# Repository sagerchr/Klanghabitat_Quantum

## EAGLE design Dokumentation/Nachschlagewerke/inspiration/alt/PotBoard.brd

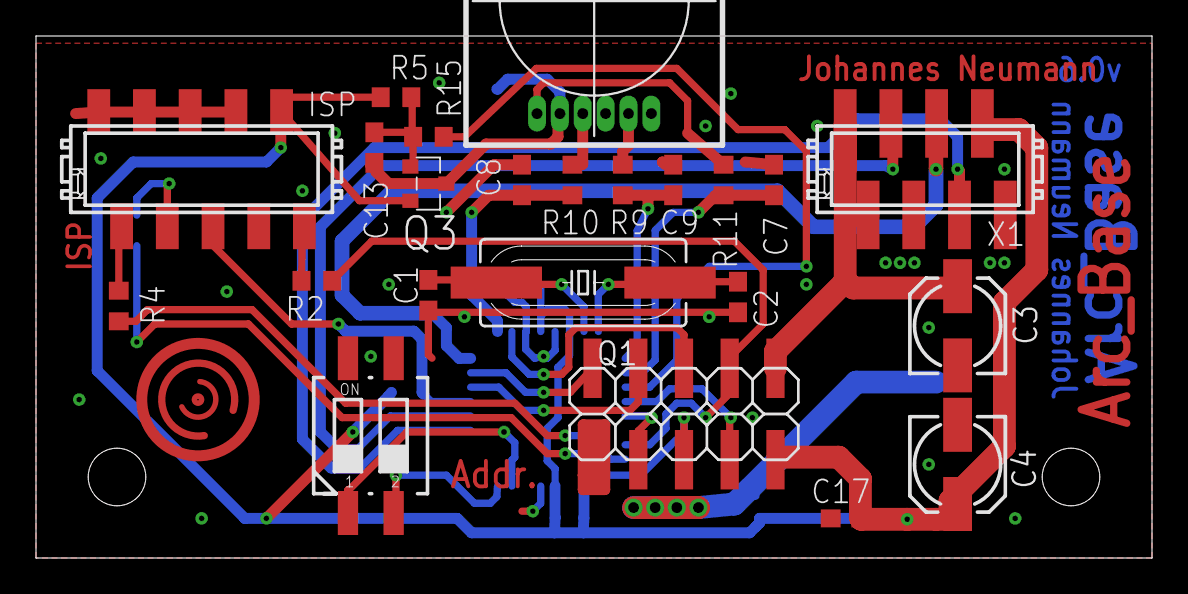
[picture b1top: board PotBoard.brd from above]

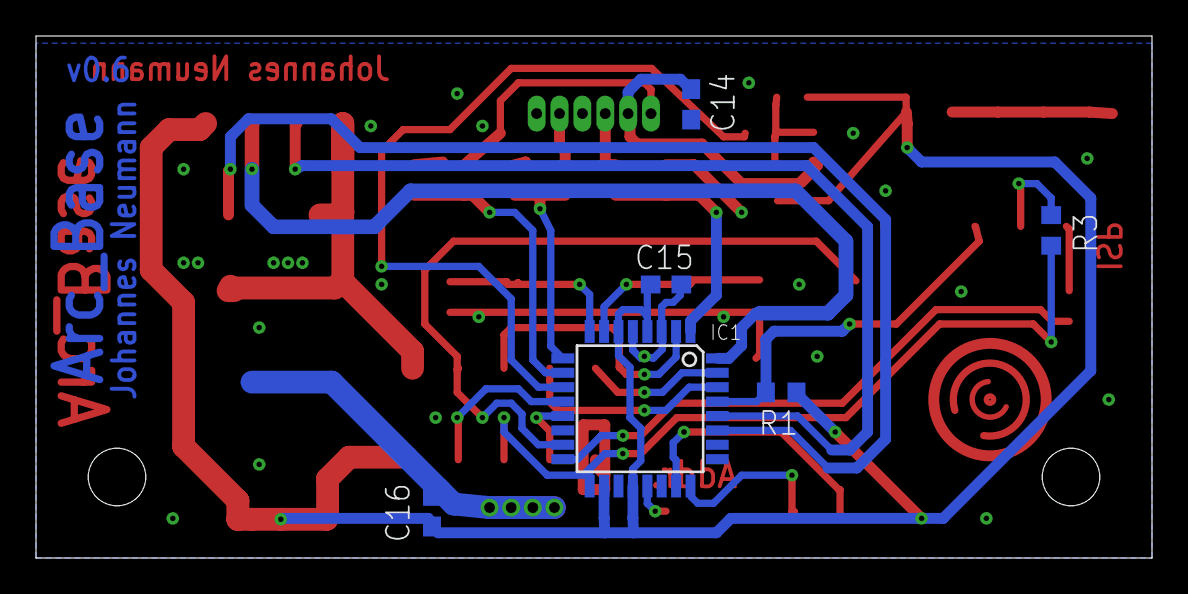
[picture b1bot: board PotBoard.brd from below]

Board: 2 copper layers, 62.0 x 29.0 mm, 29 parts (6 on the bottom side), 31 nets.

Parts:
ADRESS: 219-02; CTS-219-02
C1, C2: 22p; C0603
C3, C4: 10u; 153CLV-0505
C7, C8, C9: 10n; C0603
C13, C14, C15, C16, C17: 100n; C0603
IC1: MEGA8-AI; TQFP32-08
ISP: MICROMATCH-10-SMD
JP4: 2X05SMD
Q1: 20MHz; SM49
Q3: IRLML5203; MICRO3
R1, R5: 10k; R0603
R2, R3, R4: 330; R0603
R9, R10, R11: 4k7; R0603
R15: 1k; R0603
U$1: BOURNS_EM14; BOURNS_EM14_AXIAL
X1: MICROMATCH-8SMD; MICROMATCH-8-SMD

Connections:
+3V3: C3.+, JP4.10, X1.1, X1.2
CHANNEL-A: C9.2, IC1.9, R9.2
CHANNEL-B: C7.2, IC1.10, R11.2
GND: ADRESS.3, ADRESS.4, C1.1, C2.1, C3.-, C4.-, C7.1, C8.1, C9.1, C14.1, C15.1, C16.1, C17.1, IC1.3, IC1.5, IC1.21, ISP.P$4, ISP.P$6, ISP.P$8, ISP.P$10, JP4.1, U$1.P$1, U$1.P$3, X1.4, X1.8
GS_CLK: IC1.13, JP4.3
INT: IC1.32, X1.5
MISO: IC1.16, R4.2
MOSI: IC1.15, JP4.8, R2.2
unnamed: C1.2, IC1.7, Q1.2
unnamed: C2.2, IC1.8, Q1.1
unnamed: ISP.P$1, R2.1
unnamed: ISP.P$7, R3.1
unnamed: ISP.P$9, R4.1
unnamed: ADRESS.1, IC1.23
unnamed: ADRESS.2, IC1.24
unnamed: R11.1, U$1.P$6
unnamed: R10.1, U$1.P$4
unnamed: R9.1, U$1.P$2
unnamed: C13.2, Q3.1, R5.2, R15.1
unnamed: C13.1, C14.2, Q3.3, U$1.P$5
PWEN: IC1.11, R15.2
RCK: IC1.2, JP4.6
RESET: IC1.29, ISP.P$5, R1.2
SCK: IC1.17, JP4.5, R3.2
SCL: IC1.28, X1.3
SDA: IC1.27, X1.6
SWITCH: C8.2, IC1.1, R10.2
VCC: C4.+, C15.2, C16.2, C17.2, IC1.4, IC1.6, IC1.18, IC1.20, ISP.P$2, JP4.9, Q3.2, R1.1, R5.1, X1.7
VPRG: IC1.12, JP4.7
XERR: IC1.30, JP4.4
XLAT: IC1.31, JP4.2

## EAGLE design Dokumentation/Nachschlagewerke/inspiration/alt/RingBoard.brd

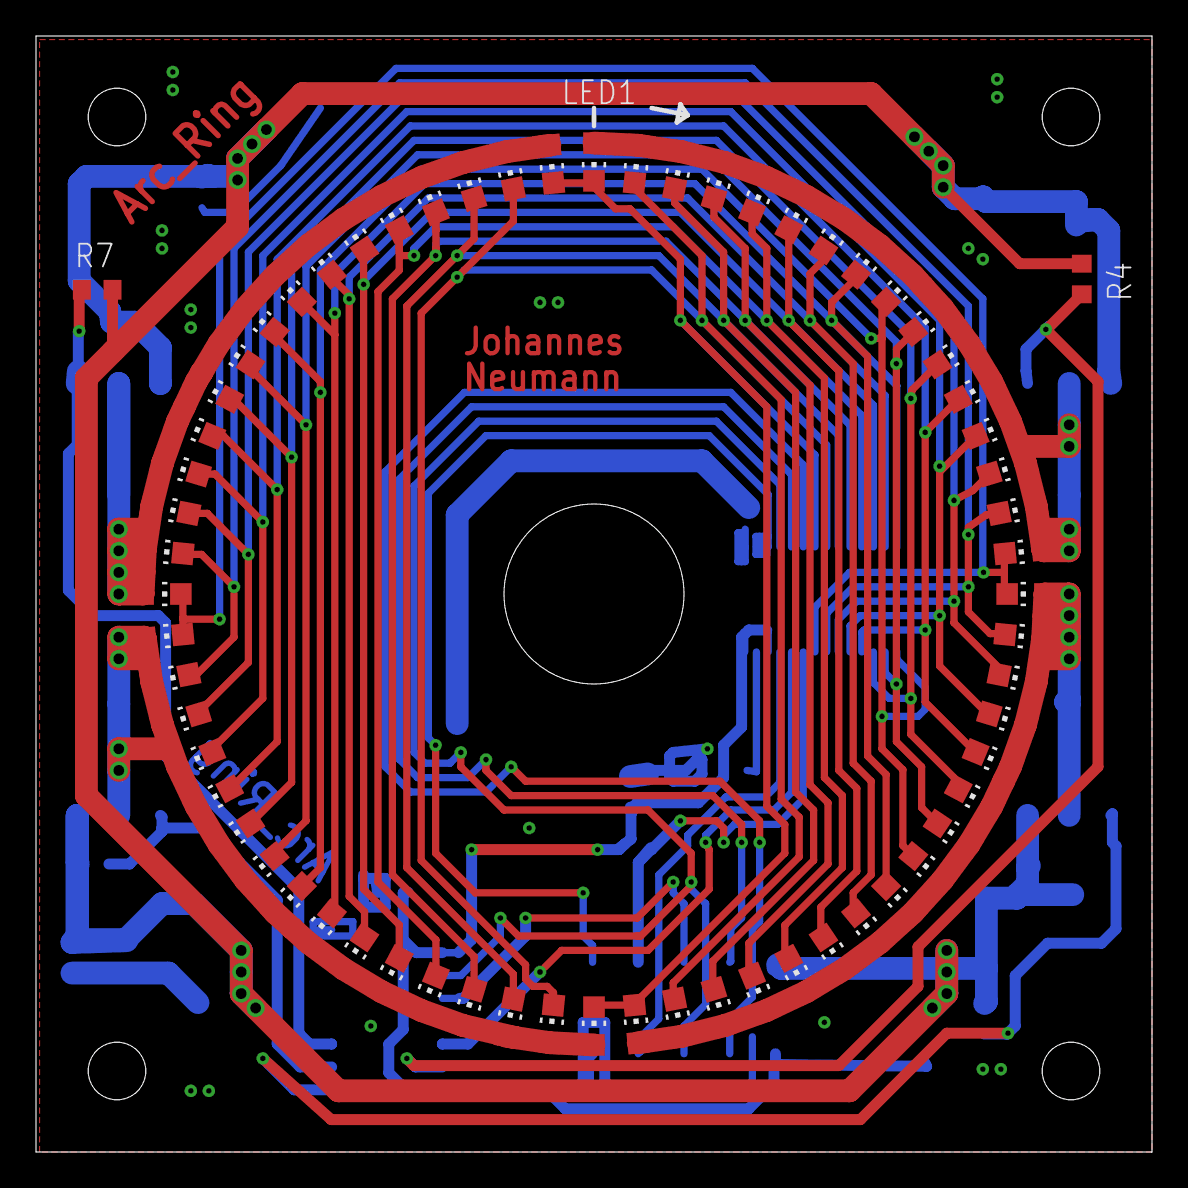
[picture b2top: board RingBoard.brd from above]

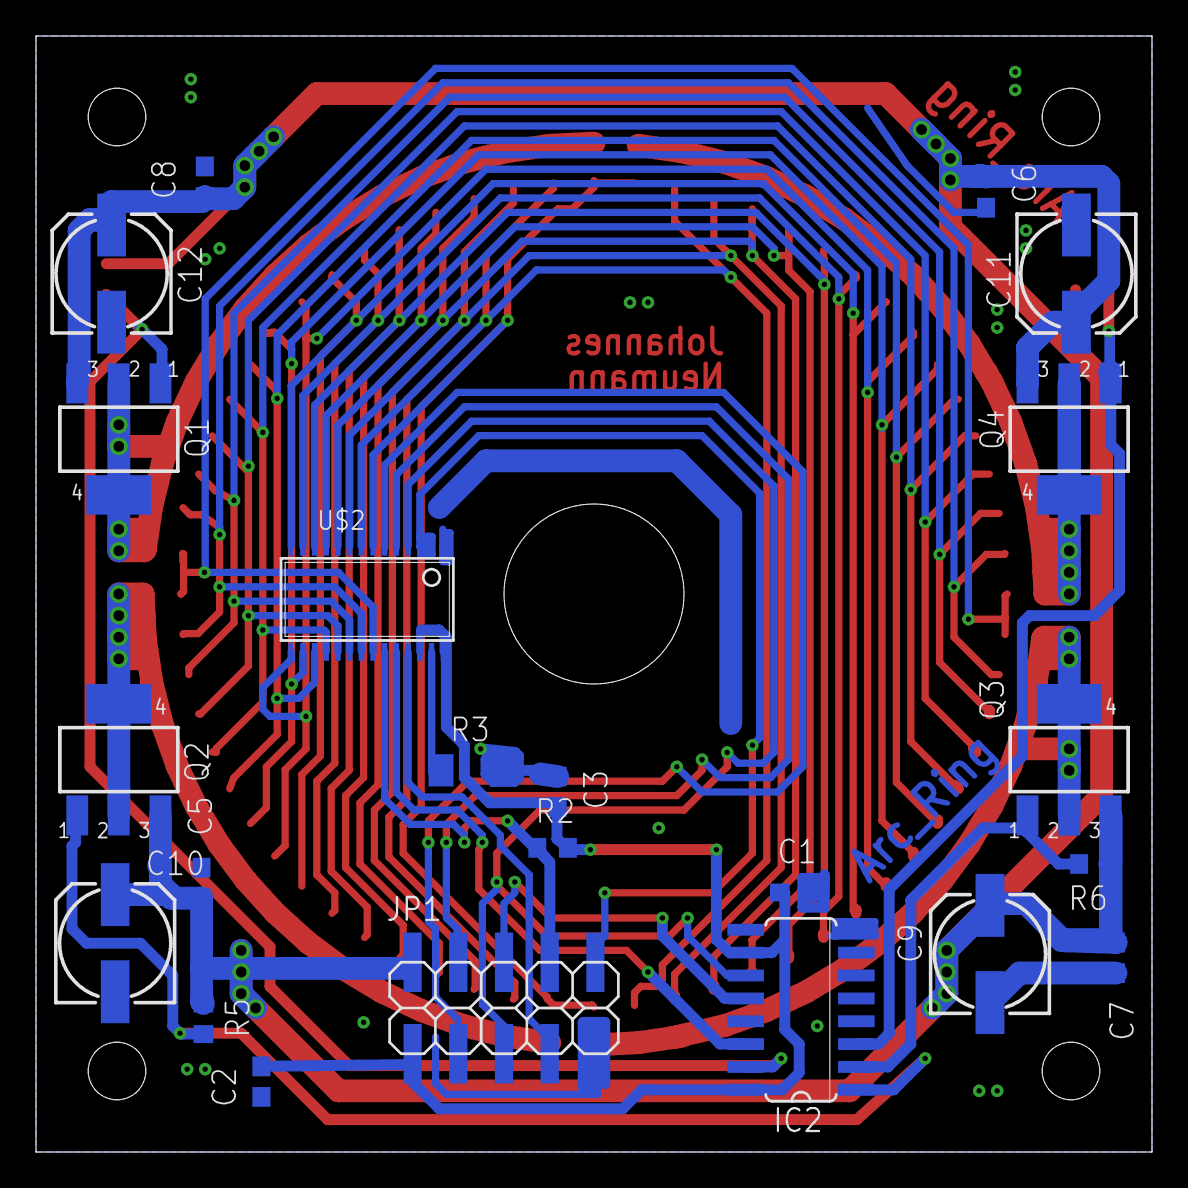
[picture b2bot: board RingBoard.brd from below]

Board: 2 copper layers, 62.0 x 62.0 mm, 88 parts (22 on the bottom side), 36 nets.

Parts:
C1, C2, C3, C5, C6, C7, C8: 100n; C0603
C9, C10, C11, C12: 10u; 153CLV-0605
IC2: 74HC595D; SO16
JP1: 2X05SMD
LED1, LED2, LED3, LED4, LED5, LED6, LED7, LED8, LED9, LED10, LED11, LED12, LED13, LED14, LED15, LED16, LED17, LED18, LED19, LED20, LED21, LED22, LED23, LED24, LED25, LED26, LED27, LED28, LED29, LED30, LED31, LED32, LED33, LED34, LED35, LED36, LED37, LED38, LED39, LED40, LED41, LED42, LED43, LED44, LED45, LED46, LED47, LED48, LED49, LED50, LED51, LED52, LED53, LED54, LED55, LED56, LED57, LED58, LED59, LED60, LED61, LED62, LED63, LED64: CHIP-LED0805
Q1, Q2, Q3, Q4: BSP171P; SOT223
R2: 10k; R0603
R3: I_SET_RESISTOR; M1406
R4, R5, R6, R7: 4k7; R0603
U$2: TLC5940-TSSOP; HTSSOP-28

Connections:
+3V3: C5.1, C6.1, C7.1, C8.1, C9.+, C10.+, C11.+, C12.+, JP1.2, Q1.3, Q2.3, Q3.3, Q4.3, R4.1, R5.1, R6.1, R7.1
COLA: IC2.15, Q1.1, R4.2
COLB: IC2.1, Q2.1, R5.2
COLC: IC2.2, Q3.1, R6.2
COLD: IC2.3, Q4.1, R7.2
D1: LED1.C, LED32.C, LED33.C, LED64.C, U$2.7
D2: LED2.C, LED31.C, LED34.C, LED63.C, U$2.8
D3: LED3.C, LED30.C, LED35.C, LED62.C, U$2.9
D4: LED4.C, LED29.C, LED36.C, LED61.C, U$2.10
D5: LED5.C, LED28.C, LED37.C, LED60.C, U$2.11
D6: LED6.C, LED27.C, LED38.C, LED59.C, U$2.12
D7: LED7.C, LED26.C, LED39.C, LED58.C, U$2.13
D8: LED8.C, LED25.C, LED40.C, LED57.C, U$2.14
D9: LED9.C, LED24.C, LED41.C, LED56.C, U$2.15
D10: LED10.C, LED23.C, LED42.C, LED55.C, U$2.16
D11: LED11.C, LED22.C, LED43.C, LED54.C, U$2.17
D12: LED12.C, LED21.C, LED44.C, LED53.C, U$2.18
D13: LED13.C, LED20.C, LED45.C, LED52.C, U$2.19
D14: LED14.C, LED19.C, LED46.C, LED51.C, U$2.20
D15: LED15.C, LED18.C, LED47.C, LED50.C, U$2.21
D16: LED16.C, LED17.C, LED48.C, LED49.C, U$2.22
GND: C1.2, C2.2, C3.2, C5.2, C6.2, C7.2, C8.2, C9.-, C10.-, C11.-, C12.-, IC2.8, IC2.13, JP1.9, R3.2, U$2.1
GS_CLK: JP1.7, U$2.25
MOSI: JP1.4, U$2.5
unnamed: IC2.14, U$2.24
unnamed: LED17.A, LED18.A, LED19.A, LED20.A, LED21.A, LED22.A, LED23.A, LED24.A, LED25.A, LED26.A, LED27.A, LED28.A, LED29.A, LED30.A, LED31.A, LED32.A, Q2.2, Q2.4
unnamed: LED33.A, LED34.A, LED35.A, LED36.A, LED37.A, LED38.A, LED39.A, LED40.A, LED41.A, LED42.A, LED43.A, LED44.A, LED45.A, LED46.A, LED47.A, LED48.A, Q3.2, Q3.4
unnamed: LED49.A, LED50.A, LED51.A, LED52.A, LED53.A, LED54.A, LED55.A, LED56.A, LED57.A, LED58.A, LED59.A, LED60.A, LED61.A, LED62.A, LED63.A, LED64.A, Q4.2, Q4.4
unnamed: LED1.A, LED2.A, LED3.A, LED4.A, LED5.A, LED6.A, LED7.A, LED8.A, LED9.A, LED10.A, LED11.A, LED12.A, LED13.A, LED14.A, LED15.A, LED16.A, Q1.2, Q1.4
unnamed: R3.1, U$2.27
RCK: IC2.12, JP1.6
SCK: IC2.11, JP1.5, U$2.4
VCC: C1.1, C2.1, C3.1, IC2.10, IC2.16, JP1.1, R2.2, U$2.26, U$2.28
VPRG: JP1.3, U$2.6
XERR: JP1.8, R2.1, U$2.23
XLAT: JP1.10, U$2.2, U$2.3

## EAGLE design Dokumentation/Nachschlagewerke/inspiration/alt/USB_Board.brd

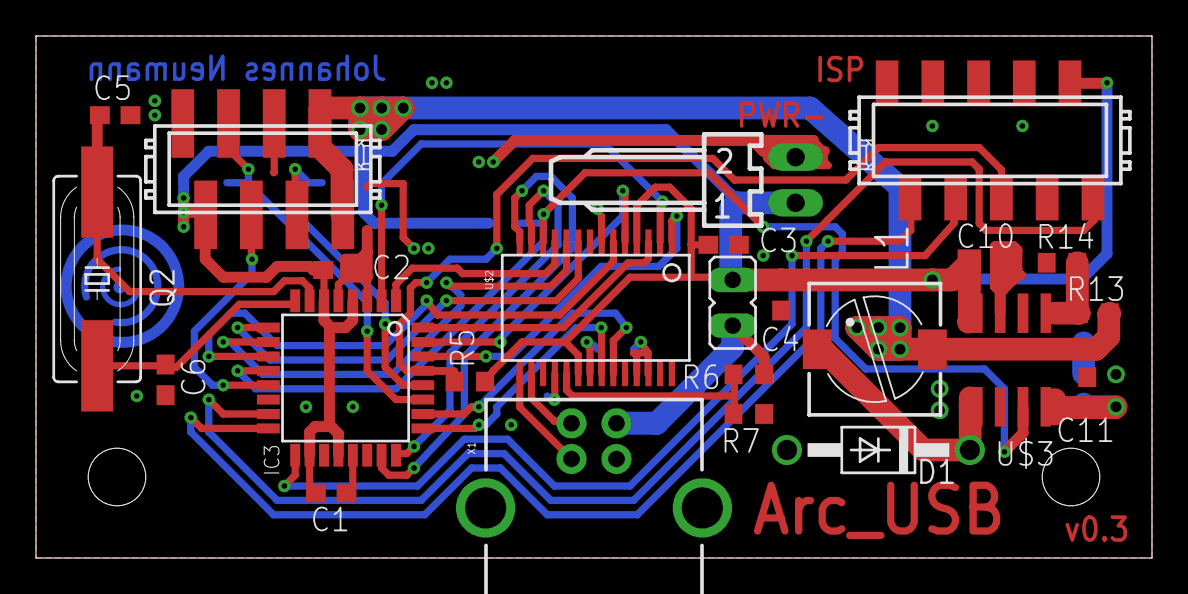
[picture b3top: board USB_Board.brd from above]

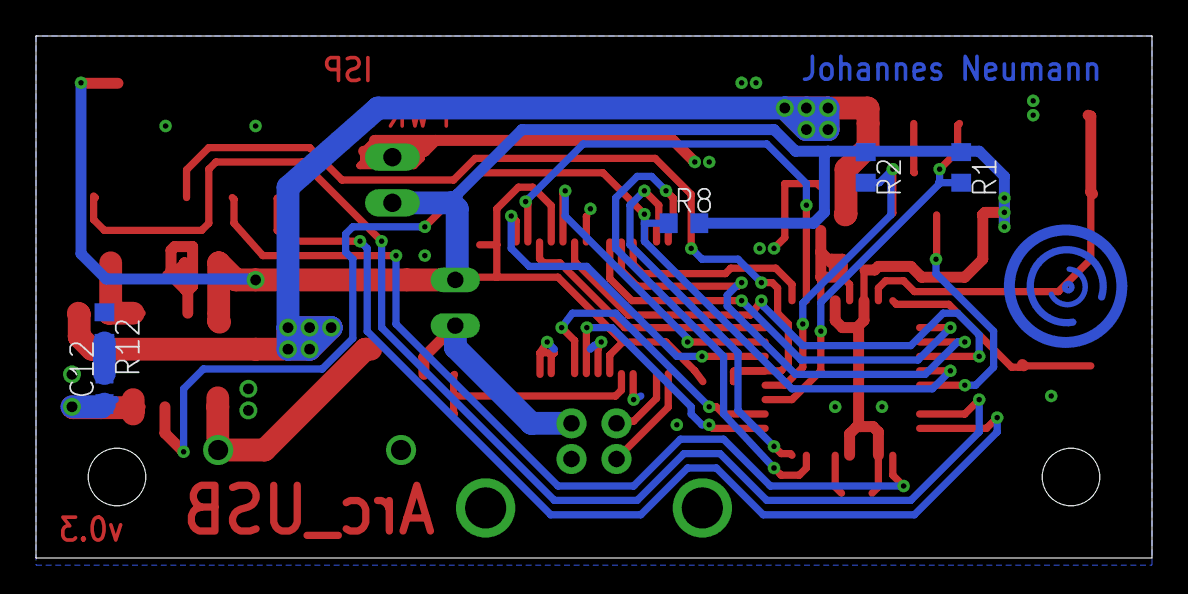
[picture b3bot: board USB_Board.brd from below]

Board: 2 copper layers, 62.0 x 29.0 mm, 29 parts (5 on the bottom side), 33 nets.

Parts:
BUS_PWRD: JP1
C1, C2, C3, C4: 100n; C0603
C5, C6: 22p; C0603
C10: 10uF; C0805
C11: 220p; C0603
C12: 22n; C0603
CONN: MICROMATCH-8SMD; MICROMATCH-8-SMD
D1: MBRS240LT3G; DO41-10
IC3: MEGA8-AI; TQFP32-08
ISP1: MICROMATCH-10-SMD
L1: 15uH; PIS2816
POWER: 22-05-7028-02; 7395-02
Q2: 20MHz; SM49
R1, R2, R14: 3k3; R0603
R5, R7, R8: 10k; R0603
R6, R12: 4k7; R0603
R13: 5k6; R0603
U$2: FT245RL; SSOP28DB
U$3: L5970AD; SO8
X1: USBPTH; USB-B-PTH

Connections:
+3V3: CONN.1, CONN.2, L1.2, R13.2
GND: C1.2, C2.2, C3.2, C4.2, C5.1, C6.1, C10.2, C11.2, CONN.4, CONN.8, D1.A, IC3.3, IC3.5, IC3.21, ISP1.P$4, ISP1.P$6, ISP1.P$8, ISP1.P$10, POWER.2, R7.1, R12.1, R14.1, U$2.7, U$2.18, U$2.21, U$2.25, U$2.26, U$3.7, X1.GND
INT: CONN.5, IC3.13
MISO_2: IC3.16, ISP1.P$9
MOSI_2: IC3.15, ISP1.P$1
unnamed: C5.2, IC3.7, Q2.2
unnamed: C6.2, IC3.8, Q2.1
unnamed: U$2.16, X1.D-
unnamed: IC3.30, U$2.1
unnamed: IC3.31, U$2.5
unnamed: IC3.32, U$2.3
unnamed: IC3.1, U$2.11
unnamed: IC3.2, U$2.2
unnamed: IC3.9, U$2.9
unnamed: IC3.10, U$2.10
unnamed: IC3.11, U$2.6
unnamed: IC3.26, U$2.23
unnamed: IC3.25, U$2.22
unnamed: IC3.24, U$2.13
unnamed: IC3.23, U$2.14
unnamed: D1.C, L1.1, U$3.1
unnamed: BUS_PWRD.2, R6.2, X1.VBUS
unnamed: R13.1, R14.2, U$3.5
unnamed: C12.2, R12.2
unnamed: C11.1, C12.1, U$3.4
PWEN: IC3.12, R8.1, U$2.12, U$3.3
PWR_ON: R6.1, R7.2, U$2.19
RESET_2: IC3.29, ISP1.P$5, R5.2
SCK_2: IC3.17, ISP1.P$7
SCL: CONN.3, IC3.28, R2.2
SDA: CONN.6, IC3.27, R1.2
USB: U$2.15, X1.D+
VCC: BUS_PWRD.1, C1.1, C2.1, C3.1, C4.1, C10.1, CONN.7, IC3.4, IC3.6, IC3.18, IC3.20, ISP1.P$2, POWER.1, R1.1, R2.1, R5.1, R8.2, U$2.4, U$2.20, U$3.8

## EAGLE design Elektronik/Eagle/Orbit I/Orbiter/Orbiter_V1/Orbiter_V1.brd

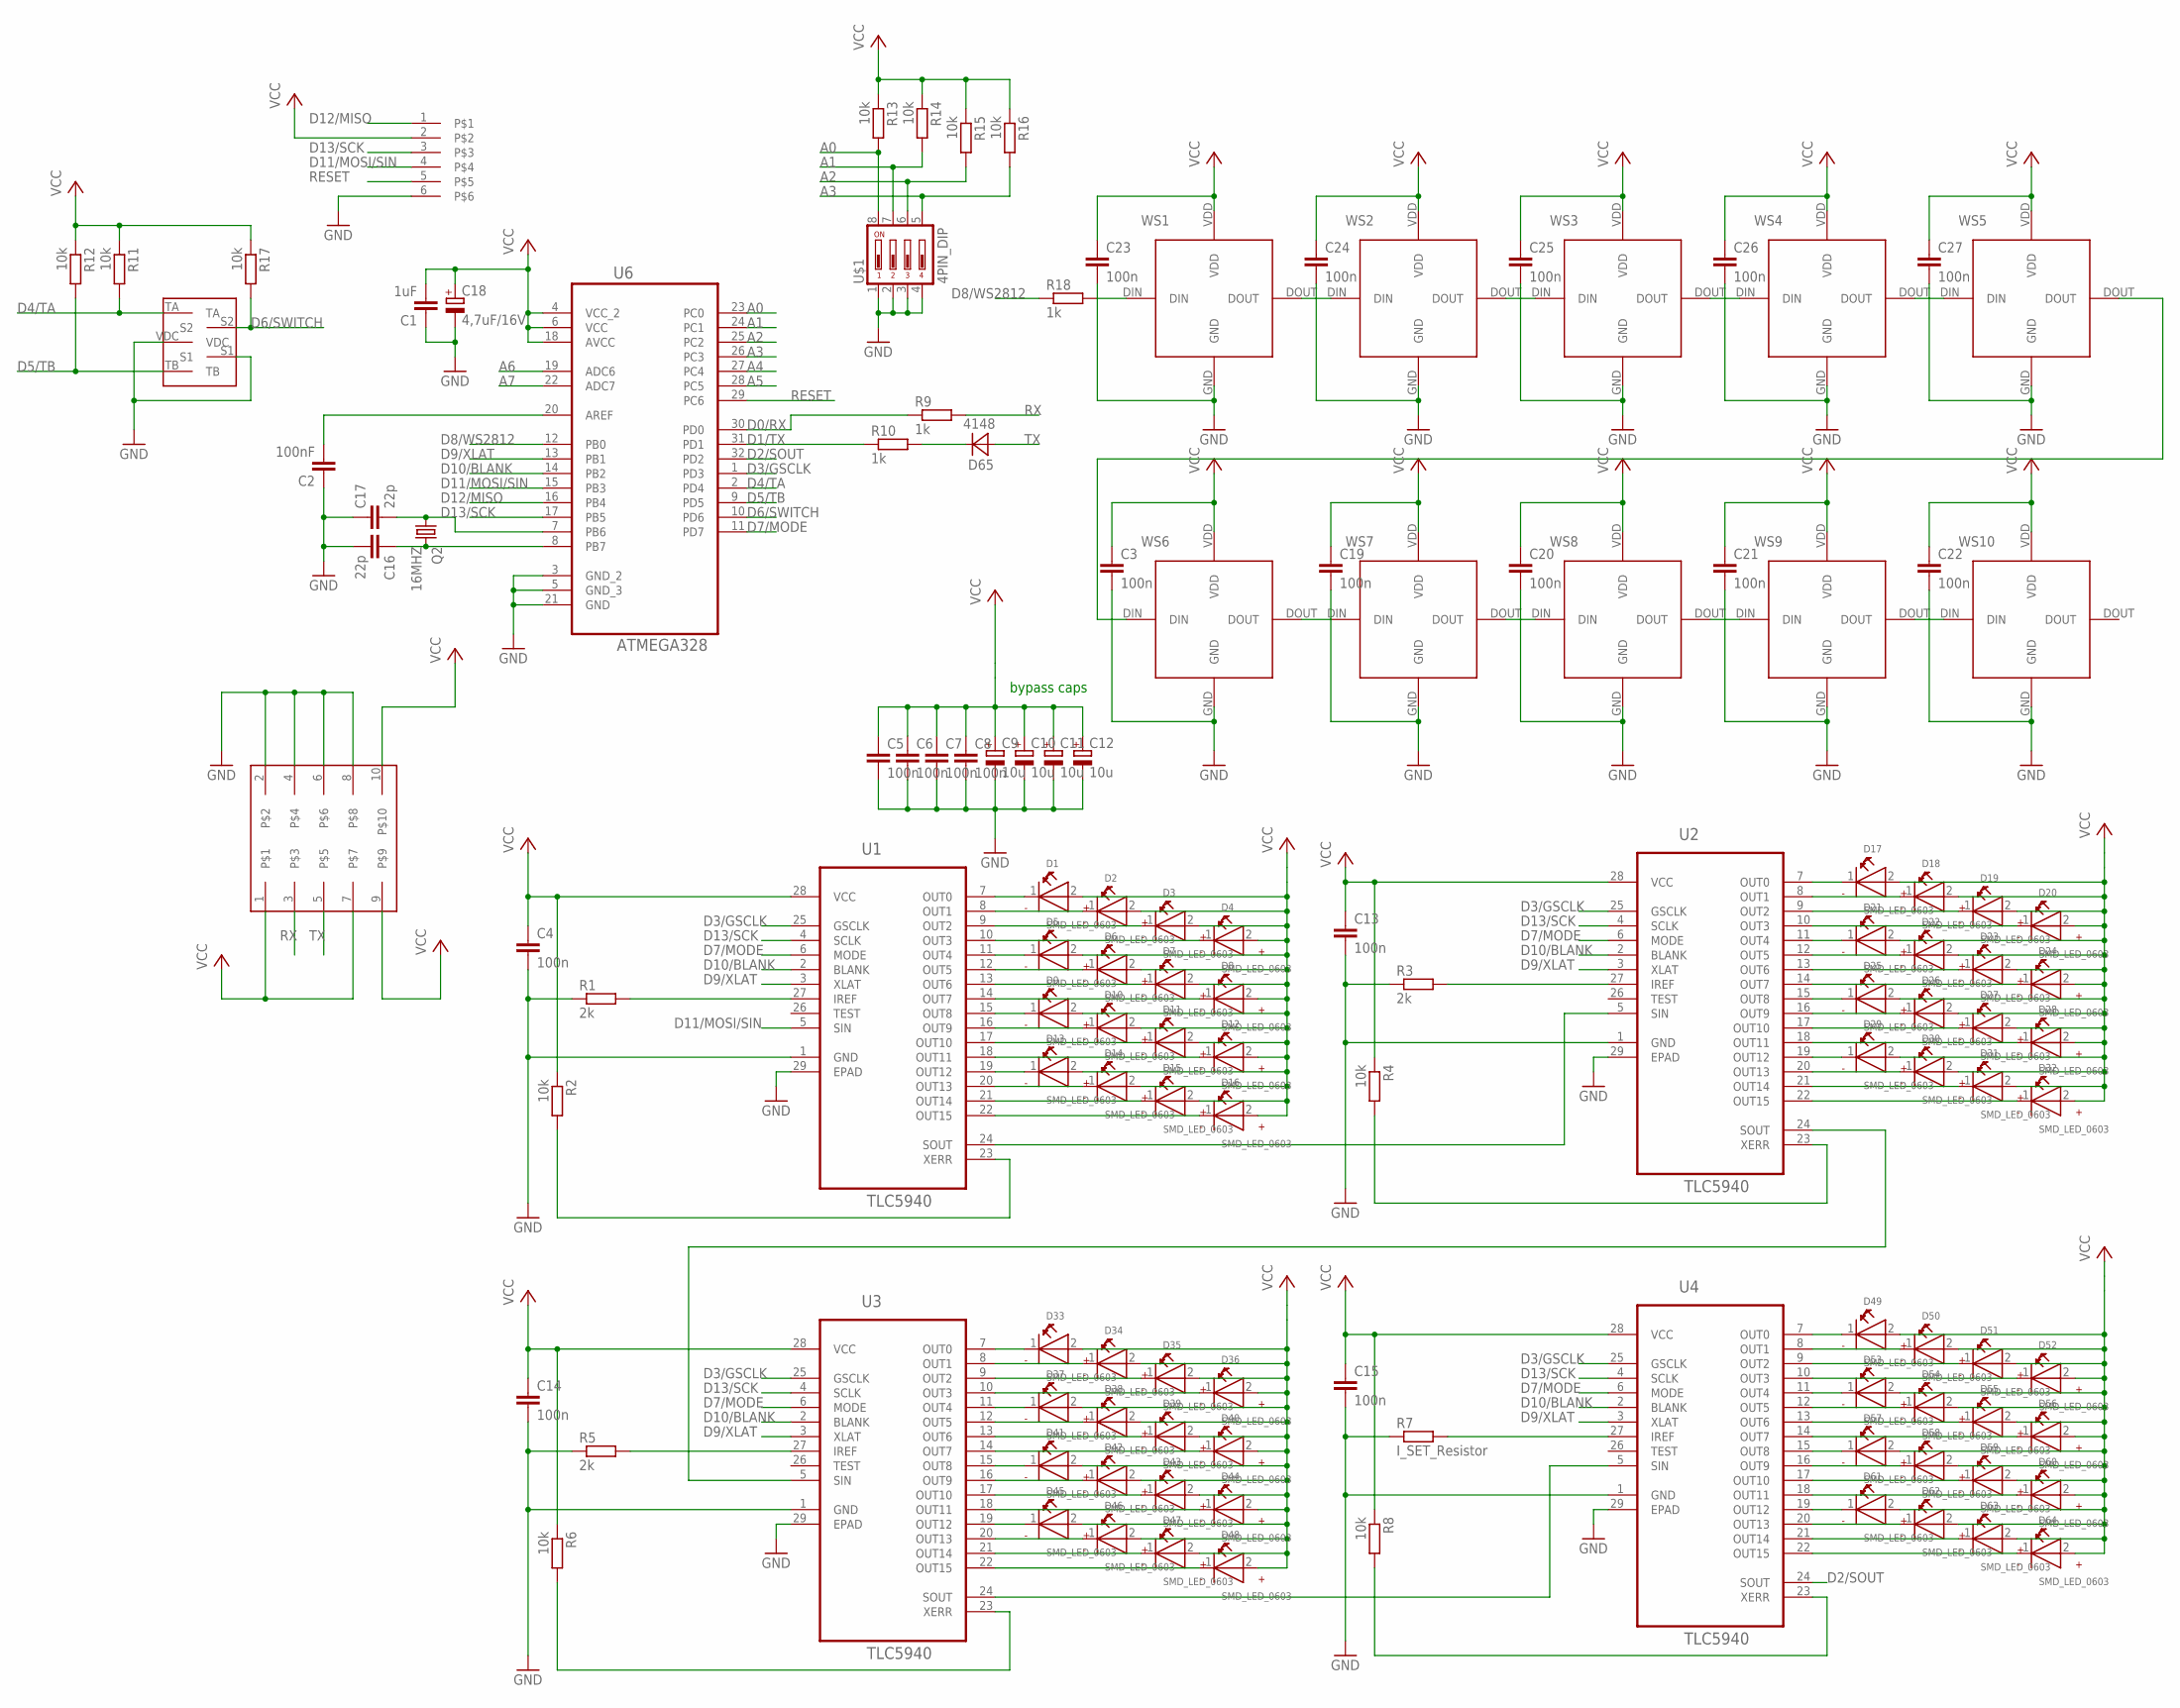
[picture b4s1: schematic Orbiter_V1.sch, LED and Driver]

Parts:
C1: 1uF; C0603
C2: 100nF; C0603
C3, C4, C5, C6, C7, C8, C13, C14, C15, C19, C20, C21, C22, C23, C24, C25, C26, C27: 100n; C0603
C9, C10, C11, C12: 10u; 153CLV-0605
C16, C17: 22p; C0603
C18: 4,7uF/16V; 153CLV-0605
D1, D2, D3, D4, D5, D6, D7, D8, D9, D10, D11, D12, D13, D14, D15, D16, D17, D18, D19, D20, D21, D22, D23, D24, D25, D26, D27, D28, D29, D30, D31, D32, D33, D34, D35, D36, D37, D38, D39, D40, D41, D42, D43, D44, D45, D46, D47, D48, D49, D50, D51, D52, D53, D54, D55, D56, D57, D58, D59, D60, D61, D62, D63, D64: SMD_LED_0603; WL-SMCW_0603
D65: 4148; SOD323-R
Q2: 16MHZ; SM49
R1, R3, R5: 2k; R0805
R2, R4, R6, R8, R11, R12, R13, R14, R15, R16, R17: 10k; R0805
R7: I_SET_Resistor; R0805
R9, R10, R18: 1k; R0805
U1, U2, U3, U4: TLC5940; SOP65P640X120-29N
U6: ATMEGA328; QFP80P900X900X120-32N
U$1: 4PIN_DIP; CTS-219-04
U$2: 10PIN_HEADER_SMD; 87832-10
U$3: 6PIN_HEADER_SMD_OPEN
U$4: BOURNS_ENCODER; BOURNS_ENCODER_SMD
WS1, WS2, WS3, WS4, WS5, WS6, WS7, WS8, WS9, WS10: WS2812

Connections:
A0: R13.2, U6.23 (PC0), U$1.8
A1: R14.2, U6.24 (PC1), U$1.7
A2: R15.2, U6.25 (PC2), U$1.6
A3: R16.2, U6.26 (PC3), U$1.5
A4: U6.27 (PC4)
A5: U6.28 (PC5)
A6: U6.19 (ADC6)
A7: U6.22 (ADC7)
D0/RX: R9.1, U6.30 (PD0)
D1/TX: R10.1, U6.31 (PD1)
D2/SOUT: U4.24 (SOUT), U6.32 (PD2)
D3/GSCLK: U1.25 (GSCLK), U2.25 (GSCLK), U3.25 (GSCLK), U4.25 (GSCLK), U6.1 (PD3)
D4/TA: R11.2, U6.2 (PD4), U$4.TA
D5/TB: R12.2, U6.9 (PD5), U$4.TB
D6/SWITCH: R17.2, U6.10 (PD6), U$4.S2
D7/MODE: U1.6 (MODE), U2.6 (MODE), U3.6 (MODE), U4.6 (MODE), U6.11 (PD7)
D8/WS2812: R18.1, U6.12 (PB0)
D9/XLAT: U1.3 (XLAT), U2.3 (XLAT), U3.3 (XLAT), U4.3 (XLAT), U6.13 (PB1)
D10/BLANK: U1.2 (BLANK), U2.2 (BLANK), U3.2 (BLANK), U4.2 (BLANK), U6.14 (PB2)
D11/MOSI/SIN: U1.5 (SIN), U6.15 (PB3), U$3.4
D12/MISO: U6.16 (PB4), U$3.1
D13/SCK: U1.4 (SCLK), U2.4 (SCLK), U3.4 (SCLK), U4.4 (SCLK), U6.17 (PB5), U$3.3
GND: C1.1, C2.1, C3.2, C4.2, C5.2, C6.2, C7.2, C8.2, C9.-, C10.-, C11.-, C12.-, C13.2, C14.2, C15.2, C16.2, C17.1, C18.-, C19.2, C20.2, C21.2, C22.2, C23.2, C24.2, C25.2, C26.2, C27.2, R1.1, R3.1, R5.1, R7.1, U1.1 (GND), U1.29 (EPAD), U2.1 (GND), U2.29 (EPAD), U3.1 (GND), U3.29 (EPAD), U4.1 (GND), U4.29 (EPAD), U6.3 (GND_2), U6.5 (GND_3), U6.21 (GND), U$1.1, U$1.2, U$1.3, U$1.4, U$2.2, U$2.4, U$2.6, U$2.8, U$3.6, U$4.S1, U$4.VDC, WS1.GND, WS2.GND, WS3.GND, WS4.GND, WS5.GND, WS6.GND, WS7.GND, WS8.GND, WS9.GND, WS10.GND
unnamed: D1.1 (-), U1.7 (OUT0)
unnamed: R1.2, U1.27 (IREF)
unnamed: D2.1 (-), U1.8 (OUT1)
unnamed: D8.1 (-), U1.14 (OUT7)
unnamed: D3.1 (-), U1.9 (OUT2)
unnamed: D9.1 (-), U1.15 (OUT8)
unnamed: D4.1 (-), U1.10 (OUT3)
unnamed: D10.1 (-), U1.16 (OUT9)
unnamed: D5.1 (-), U1.11 (OUT4)
unnamed: D6.1 (-), U1.12 (OUT5)
unnamed: D7.1 (-), U1.13 (OUT6)
unnamed: D11.1 (-), U1.17 (OUT10)
unnamed: D12.1 (-), U1.18 (OUT11)
unnamed: D13.1 (-), U1.19 (OUT12)
unnamed: D14.1 (-), U1.20 (OUT13)
unnamed: D15.1 (-), U1.21 (OUT14)
unnamed: D16.1 (-), U1.22 (OUT15)
unnamed: R2.2, U1.23 (XERR)
unnamed: D17.1 (-), U2.7 (OUT0)
unnamed: D18.1 (-), U2.8 (OUT1)
unnamed: D19.1 (-), U2.9 (OUT2)
unnamed: D20.1 (-), U2.10 (OUT3)
unnamed: D21.1 (-), U2.11 (OUT4)
unnamed: D22.1 (-), U2.12 (OUT5)
unnamed: D23.1 (-), U2.13 (OUT6)
unnamed: D24.1 (-), U2.14 (OUT7)
unnamed: D25.1 (-), U2.15 (OUT8)
unnamed: D26.1 (-), U2.16 (OUT9)
unnamed: D27.1 (-), U2.17 (OUT10)
unnamed: U1.24 (SOUT), U2.5 (SIN)
unnamed: D28.1 (-), U2.18 (OUT11)
unnamed: D29.1 (-), U2.19 (OUT12)
unnamed: D30.1 (-), U2.20 (OUT13)
unnamed: D31.1 (-), U2.21 (OUT14)
unnamed: D32.1 (-), U2.22 (OUT15)
unnamed: R3.2, U2.27 (IREF)
unnamed: R4.2, U2.23 (XERR)
unnamed: U2.24 (SOUT), U3.5 (SIN)
unnamed: D33.1 (-), U3.7 (OUT0)
unnamed: D34.1 (-), U3.8 (OUT1)
unnamed: D35.1 (-), U3.9 (OUT2)
unnamed: D36.1 (-), U3.10 (OUT3)
unnamed: D37.1 (-), U3.11 (OUT4)
unnamed: D38.1 (-), U3.12 (OUT5)
unnamed: D39.1 (-), U3.13 (OUT6)
unnamed: D40.1 (-), U3.14 (OUT7)
unnamed: D41.1 (-), U3.15 (OUT8)
unnamed: D42.1 (-), U3.16 (OUT9)
unnamed: D43.1 (-), U3.17 (OUT10)
unnamed: D44.1 (-), U3.18 (OUT11)
unnamed: D45.1 (-), U3.19 (OUT12)
unnamed: D46.1 (-), U3.20 (OUT13)
unnamed: D47.1 (-), U3.21 (OUT14)
unnamed: D48.1 (-), U3.22 (OUT15)
unnamed: R5.2, U3.27 (IREF)
unnamed: R6.2, U3.23 (XERR)
unnamed: U3.24 (SOUT), U4.5 (SIN)
unnamed: D49.1 (-), U4.7 (OUT0)
unnamed: D50.1 (-), U4.8 (OUT1)
unnamed: D51.1 (-), U4.9 (OUT2)
unnamed: D52.1 (-), U4.10 (OUT3)
unnamed: D53.1 (-), U4.11 (OUT4)
unnamed: D54.1 (-), U4.12 (OUT5)
unnamed: D55.1 (-), U4.13 (OUT6)
unnamed: D56.1 (-), U4.14 (OUT7)
unnamed: D57.1 (-), U4.15 (OUT8)
unnamed: D58.1 (-), U4.16 (OUT9)
unnamed: D59.1 (-), U4.17 (OUT10)
unnamed: D60.1 (-), U4.18 (OUT11)
unnamed: D61.1 (-), U4.19 (OUT12)
unnamed: D62.1 (-), U4.20 (OUT13)
unnamed: D63.1 (-), U4.21 (OUT14)
unnamed: D64.1 (-), U4.22 (OUT15)
unnamed: R7.2, U4.27 (IREF)
unnamed: R8.2, U4.23 (XERR)
unnamed: WS1.DOUT, WS2.DIN
unnamed: D65.C, R10.2
unnamed: R18.2, WS1.DIN
unnamed: WS2.DOUT, WS3.DIN
unnamed: WS3.DOUT, WS4.DIN
unnamed: C17.2, Q2.1, U6.7 (PB6)
unnamed: C16.1, Q2.2, U6.8 (PB7)
unnamed: WS4.DOUT, WS5.DIN
unnamed: WS5.DOUT, WS6.DIN
unnamed: WS6.DOUT, WS7.DIN
unnamed: WS7.DOUT, WS8.DIN
unnamed: WS8.DOUT, WS9.DIN
unnamed: WS9.DOUT, WS10.DIN
unnamed: C2.2, U6.20 (AREF)
RESET: U6.29 (PC6), U$3.5
RX: R9.2, U$2.3
TX: D65.A, U$2.5
VCC: C1.2, C3.1, C4.1, C5.1, C6.1, C7.1, C8.1, C9.+, C10.+, C11.+, C12.+, C13.1, C14.1, C15.1, C18.+, C19.1, C20.1, C21.1, C22.1, C23.1, C24.1, C25.1, C26.1, C27.1, D1.2 (+), D2.2 (+), D3.2 (+), D4.2 (+), D5.2 (+), D6.2 (+), D7.2 (+), D8.2 (+), D9.2 (+), D10.2 (+), D11.2 (+), D12.2 (+), D13.2 (+), D14.2 (+), D15.2 (+), D16.2 (+), D17.2 (+), D18.2 (+), D19.2 (+), D20.2 (+), D21.2 (+), D22.2 (+), D23.2 (+), D24.2 (+), D25.2 (+), D26.2 (+), D27.2 (+), D28.2 (+), D29.2 (+), D30.2 (+), D31.2 (+), D32.2 (+), D33.2 (+), D34.2 (+), D35.2 (+), D36.2 (+), D37.2 (+), D38.2 (+), D39.2 (+), D40.2 (+), D41.2 (+), D42.2 (+), D43.2 (+), D44.2 (+), D45.2 (+), D46.2 (+), D47.2 (+), D48.2 (+), D49.2 (+), D50.2 (+), D51.2 (+), D52.2 (+), D53.2 (+), D54.2 (+), D55.2 (+), D56.2 (+), D57.2 (+), D58.2 (+), D59.2 (+), D60.2 (+), D61.2 (+), D62.2 (+), D63.2 (+), D64.2 (+), R2.1, R4.1, R6.1, R8.1, R11.1, R12.1, R13.1, R14.1, R15.1, R16.1, R17.1, U1.28 (VCC), U2.28 (VCC), U3.28 (VCC), U4.28 (VCC), U6.4 (VCC_2), U6.6 (VCC), U6.18 (AVCC), U$2.1, U$2.7, U$2.9, U$2.10, U$3.2, WS1.VDD, WS2.VDD, WS3.VDD, WS4.VDD, WS5.VDD, WS6.VDD, WS7.VDD, WS8.VDD, WS9.VDD, WS10.VDD

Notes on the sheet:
bypass caps

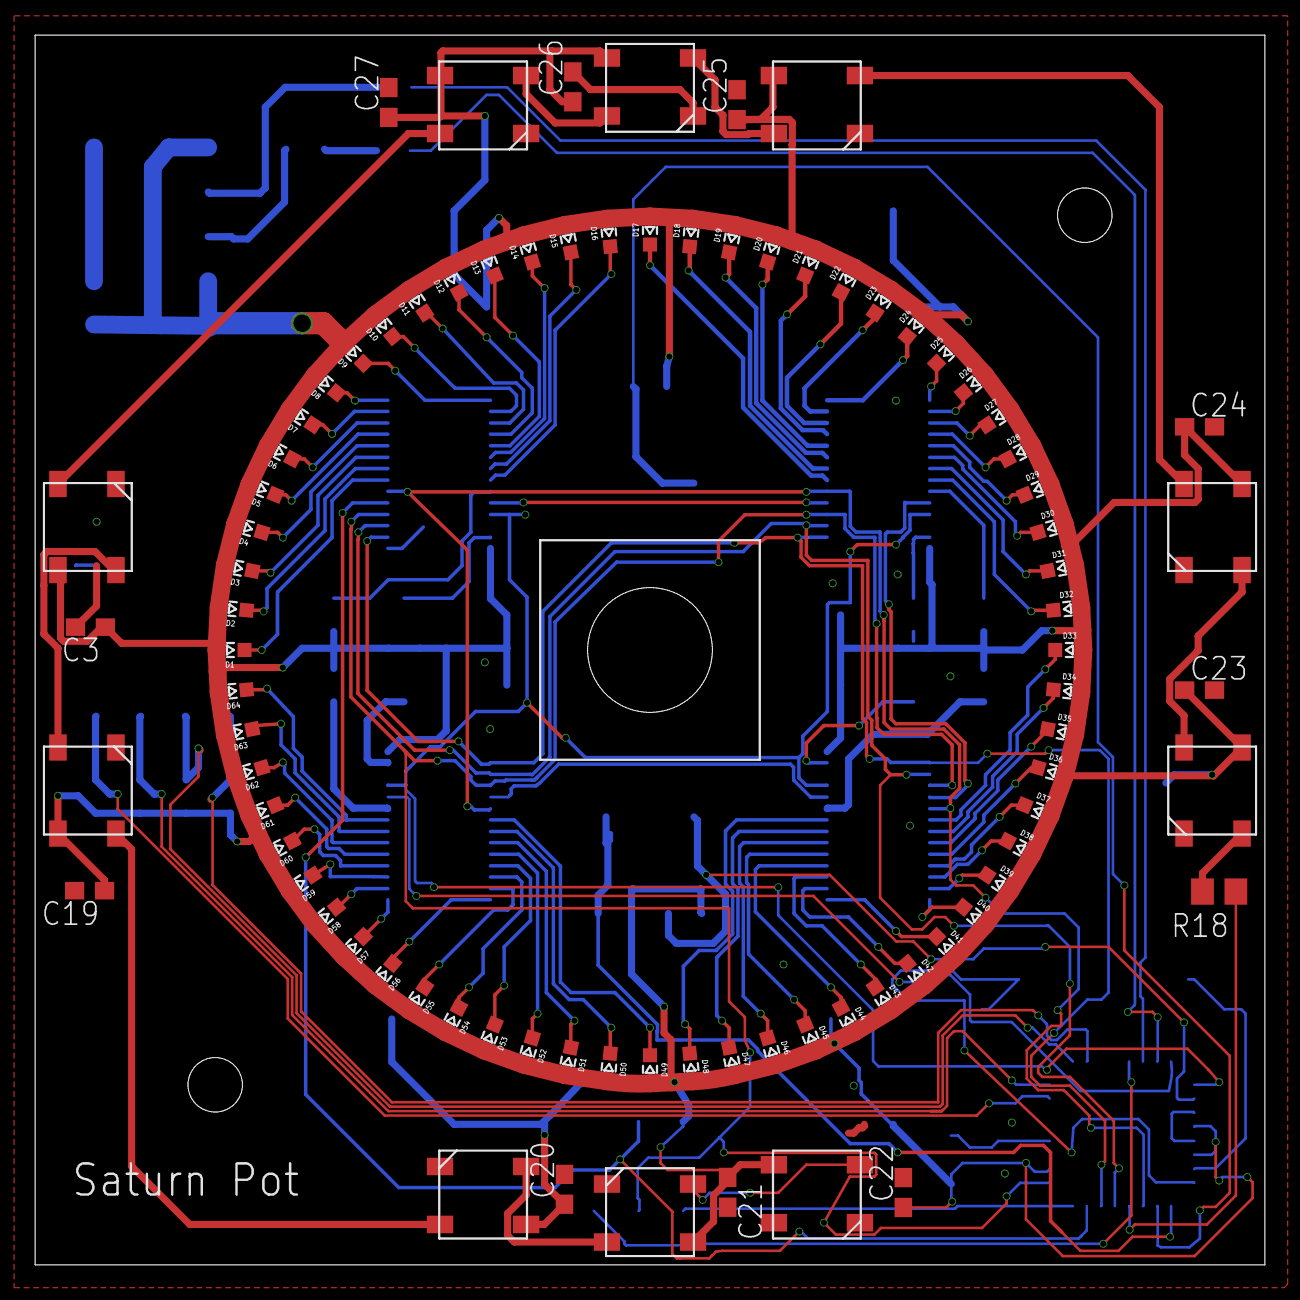
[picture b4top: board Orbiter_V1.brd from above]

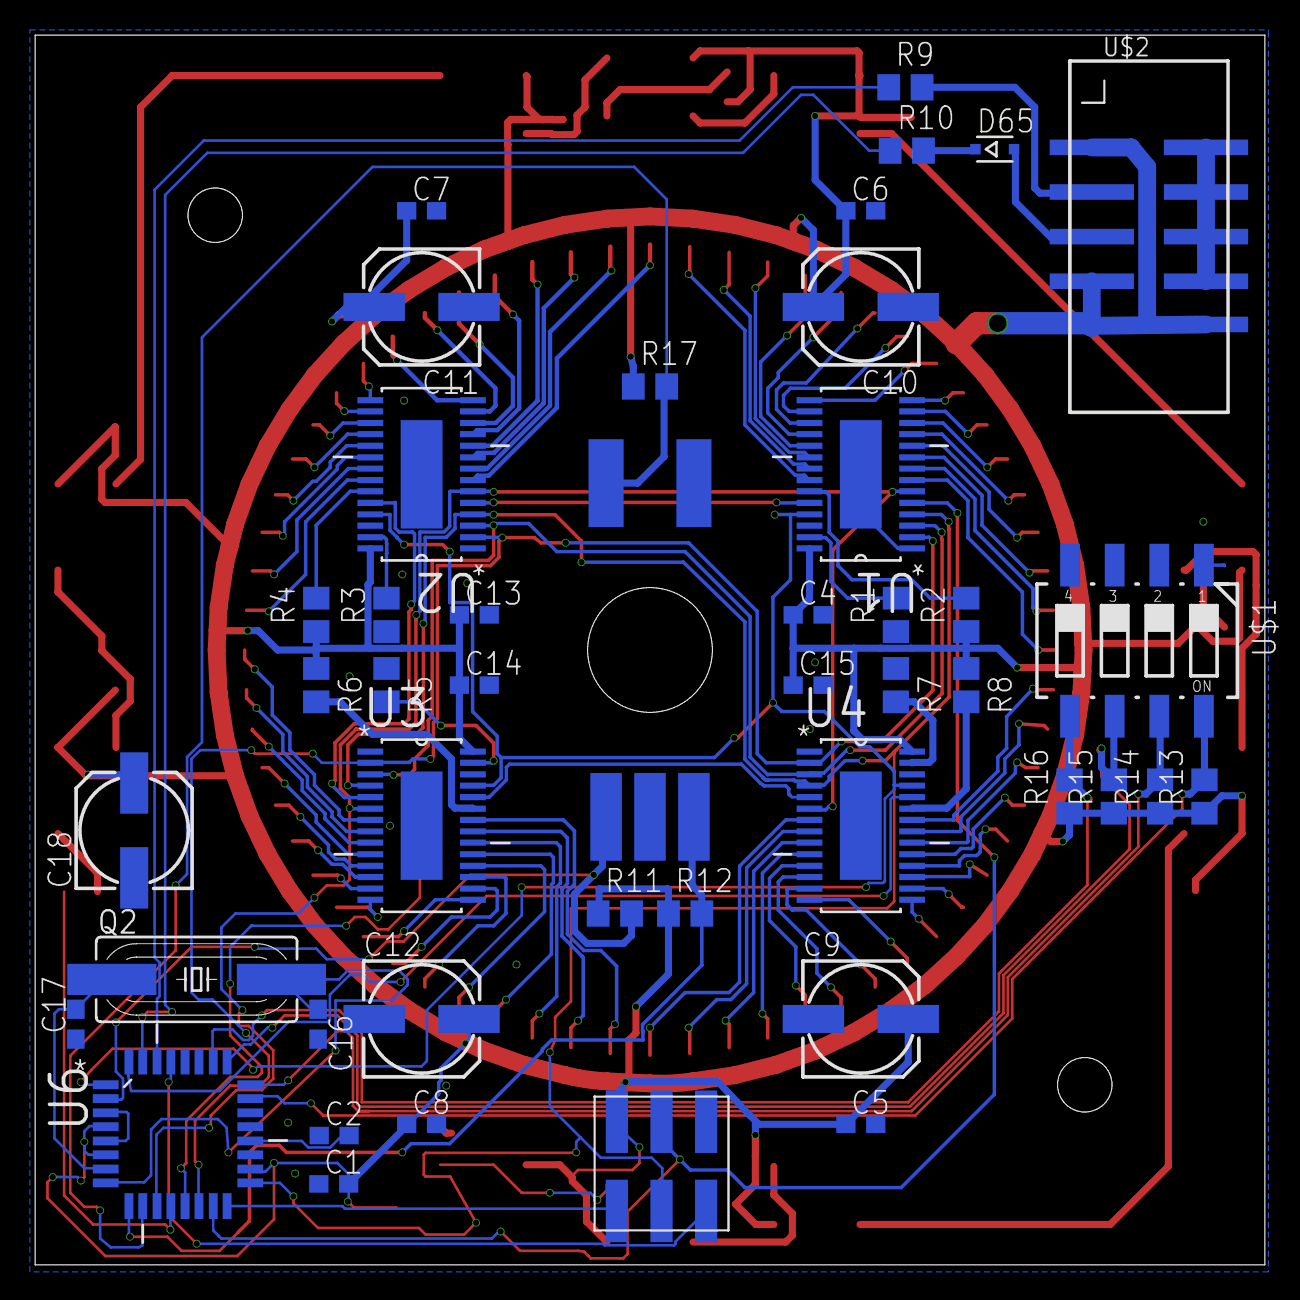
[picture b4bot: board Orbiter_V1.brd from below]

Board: 2 copper layers, 70.0 x 70.0 mm, 130 parts (44 on the bottom side), 112 nets.
